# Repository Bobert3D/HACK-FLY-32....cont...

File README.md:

# HACK FLY 32 (3 inch fpv drone using esp32 s3)

A compact 3-inch 3D printed FPV drone designed for efficiency, stability, and extended flight time. This project features a custom-built flight controller, ExpressLRS (ELRS) communication, and GPS support, all running on Betaflight firmware.

**[Zine link](/docs/ZINE/HACK%20FLY%20ZINE.pdf)**

⚠️ Disclaimer
The use and operation of this drone may require licenses in certain countries. This project is experimental and provided without any guarantee of safety or reliability and it's under the [CERN Open Hardware Licence version 2-Strongly reciprocal ](/license), and the firmware ESP-FLY is under the MIT license.

USE AT YOUR OWN RISK.

# Specifications

Frame Size: 3-inch.

Motors: 1104 – 4300KV- (remix uses IFlight XING2 1404 4600KV!)

Propeller: Gemfan 3018 bi-blade(possible tri blade!).

Battery Support: 3S ONLY if running XING2 at 4600KV!! LiPo.

Suggested Batt: (900-1500)mah 3s lipo.

Flight Controller: Custom-designed FC. (Read more below!)

Firmware: Betaflight(not native running via ESP-FC)!

RC Protocol: ExpressLRS (ELRS)

Navigation: GPS supported.

GPS compatibility: Any 15*15mm gps (HGLRS M100 Mini suggested)

Use Case: Long-range FPV, but mostly FPV 4k cinematic action and camera.

# Why Hack Fly????

A custom hardware build including a PCB that gives you your own way to add spice to it!
Also compatible with BetaFlight (you can achieve very agile and stable flight characteristics). Supports all types of Radio RX protocols: PPM, SBUS, IBUS, and CRSF Receivers.
If you combine it with a high-performance 18650 Li-ion battery (like Molicel PB28A,Eve 30pl,Ampace jp30 or Sony vt6), you can get over 10 minutes of flight time!

Who doesn't want their drone to be repairable? The 3D-printed frame gives you that flexibility.
Break the frame in a crash? Just print another. Cost? Less than $1 even if you use PETG-CF.

# Documentation
In this repository, you can find 3D printable STL files, Garber and all the other
files to build your own flight controller and Drone frame. 
For flashing the latest Betaflight to the Flight controller visit rtlopez/esp-fc repo- 
**https://github.com/rtlopez/esp-fc**.

# Quick Start

## Requirements

## Hardware:

* Seeed Studio Xiao ESP32 S3(https://www.seeedstudio.com/XIAO-ESP32S3-p-5627.html)
* 1104 4300kv motor (or XIN 1404 4600KV, I used those!) x4 (https://shop.iflight.com/index.php?route=product/product&product_id=3382)
* 2-3S micro 8A ESC (or my custom PCB!) x4 (https://s.click.aliexpress.com/e/_c4ShBcjr)
> [!IMPORTANT]
> **If you also want build your own 4in1 esc**, Visit this repo- **https://github.com/minhazislamnafi/Nano-2-3s-AM32-ESC**.
* Gemfan 3018 bi-blade × 2 pair (https://s.click.aliexpress.com/e/_c34qvZlJ)
* Hglrc m100 mini GPS (https://s.click.aliexpress.com/e/_c4F9Fw8h)
* HGLRC Zeus Nano VTX 350mW (https://s.click.aliexpress.com/e/_c3wNfnSD)
* 2.54mm Round Hole Needle Female & Male Pin Header (https://s.click.aliexpress.com/e/_c327hfoV)
* For VRX buy any good 5.8ghz analog goggles (ranging from 70-300$) or Checkout Artlink digital system

**Components:**

* Mpu6050M QFN-24 (https://s.click.aliexpress.com/e/_c2JBpdQt)
* 0402 10uH inductor (https://s.click.aliexpress.com/e/_c3vbFmHj)
* Some 0603 size Resistors and capacitors [**Checkout Bill of material**](/Flight%20Controller/PCB/BOM_HACK_FLY_V1.2_2026-04-11.csv)
(https://a.aliexpress.com/_c3XHJm1T)
* 0805 size red & green led ×2
(https://s.click.aliexpress.com/e/_c3fRfz0V)

## For detailed parts list and prices follow [BOM](docs/Bill%20of%20material/BOM.md) ##

## PCB

Use JLCPCB if you're in ASIA or PCBWAY if you're in America. Also, find what manufacturer is better for you. 
If you just want to get Flight controller PCB then use this [**GERBER file**](/Flight%20Controller/PCB/Gerber_HACK_FLY_PCB_V1.2_2026-04-11.zip). Download it and place order.
Or if you just want to build your own PCB, then follow this [**Schematic**](/Flight%20Controller/PCB/Schematic_HACK_FLY_2026-04-11.svg).

## CAD Render

## Full Onshape CAD [link](https://cad.onshape.com/documents/91570ca427478f6ae70e01eb/w/492acaa76972d9ee5b32506f/e/992fe092f0691e5ff67f2b14?renderMode=0&uiState=69eeb3fd4989f512fbb6f874)/[Full assembly](https://cad.onshape.com/documents/91570ca427478f6ae70e01eb/w/492acaa76972d9ee5b32506f/e/0d19368f0521a092eb10a81c?renderMode=0&uiState=69feb6588dc385fd419da8b7)

To print all the parts for the HACK FLY frame, please **USE**

**PETG or ABS** - [Top plate](/Drone%20Frame/Top%20Plate/Top%20plate.stl), [Bottom plate](/Drone%20Frame/Bottom%20plate).(**better to use PETG-CF**)

**TPU** - [Camera mount](/Drone%20Frame/Camera%20Mount/Camera%20mount%20right.stl), [GPS mount](/Drone%20Frame/GPS%20mount/GPS%20mount.stl), [VTXantena mount](/Drone%20Frame/Vtx%20antena%20mount/Antenna%20mount.stl).

## IRL

## Wiring Diagram ##

## AFTER EVERYTHING IS DONE SOURCING, FOLLOW THESE STEPS ##

**1. Spend some money $$ to buy the parts mentioned in [BOM](docs/Bill%20of%20material/BOM.md).**

**2. Order the Flight controller PCB using this [GERBER file](/Flight%20Controller/PCB/Gerber_HACK_FLY_PCB_V1.2_2026-04-11.zip).**

**3. Solder the SMD components of the PCB by hand ;) Or just order the PCBs with SMT services.**

**4. Using the wiring diagram, solder the ESCs and battery connector to the PCB.**

**5. crucial step: assemble everything. ( I will add every assembly step, once I have built IRL:)**

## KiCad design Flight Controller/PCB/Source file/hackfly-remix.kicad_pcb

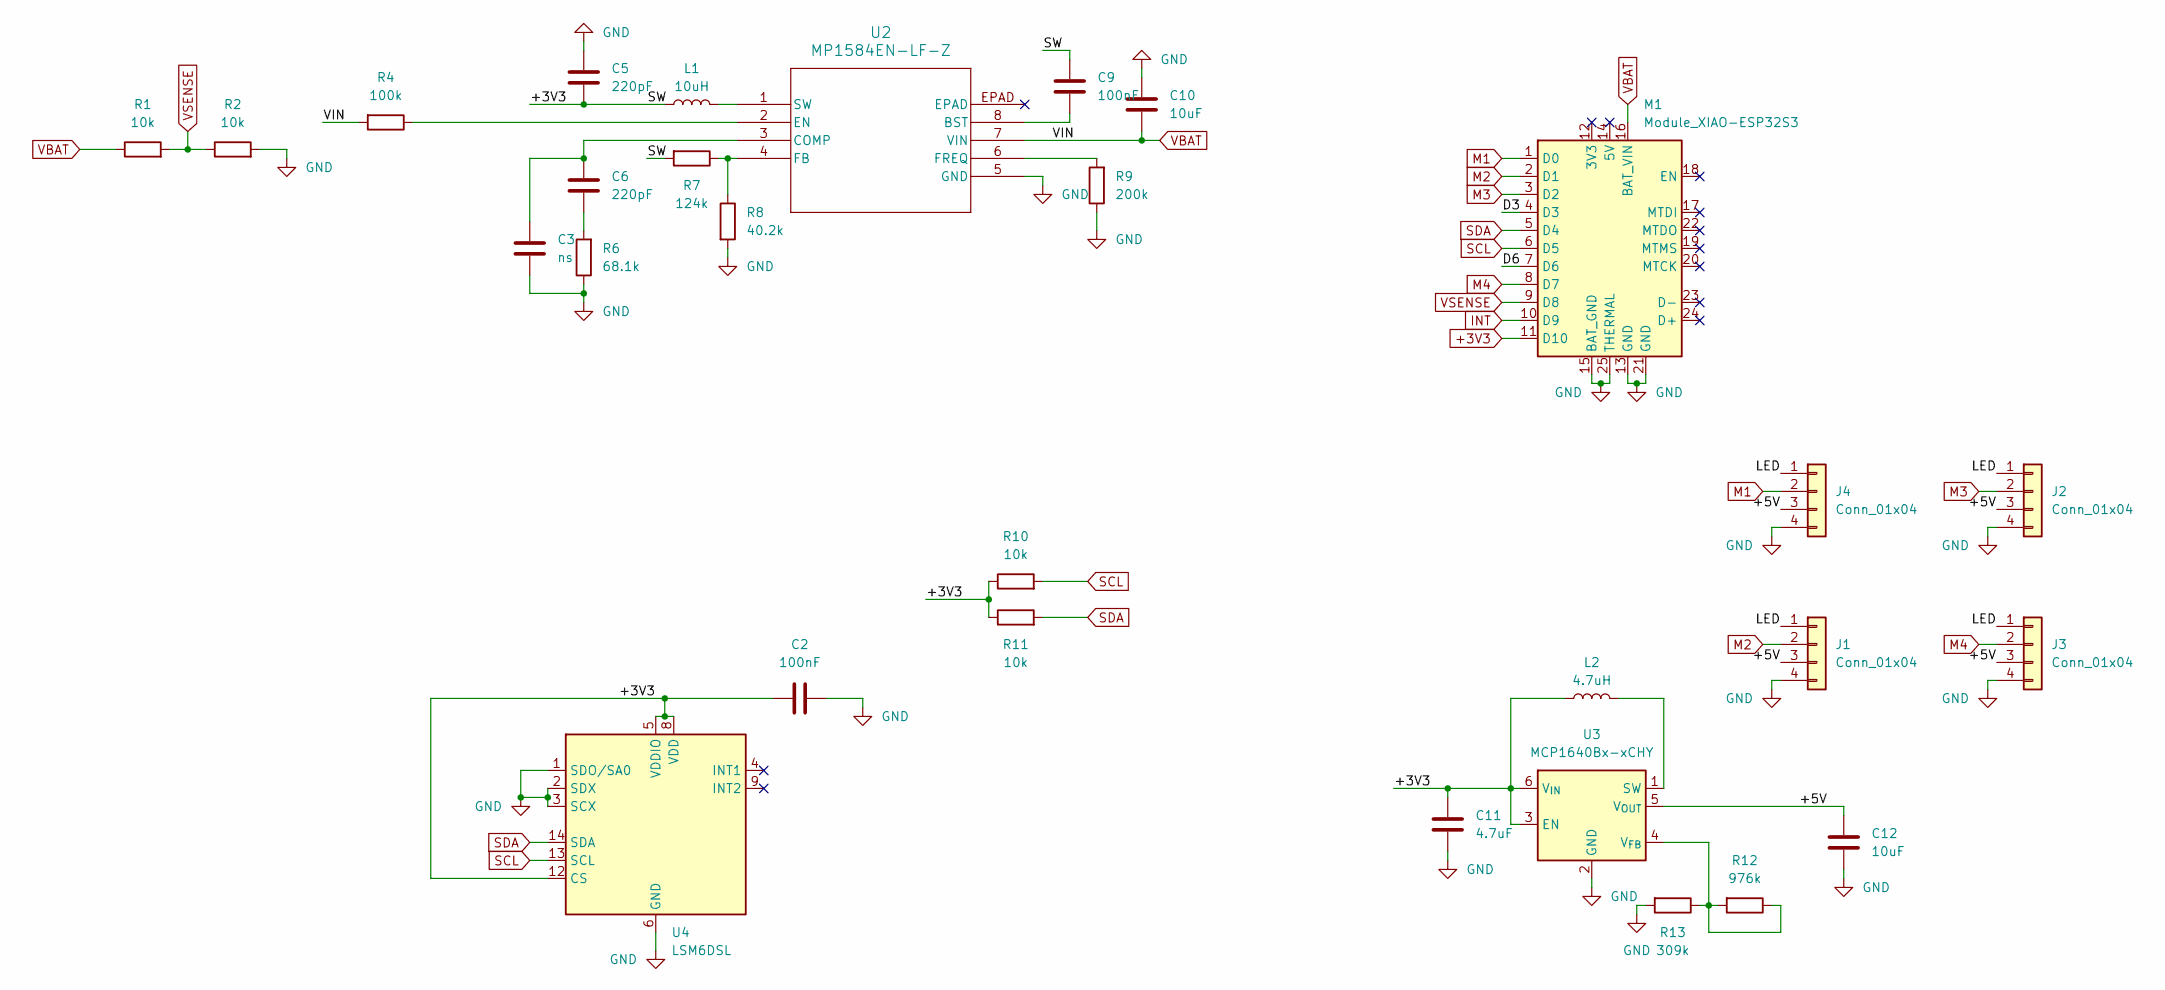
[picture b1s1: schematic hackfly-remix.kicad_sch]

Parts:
C2, C9: 100nF; C_0805_2012Metric
C3: ns; C_0805_2012Metric
C5, C6: 220pF; C_0805_2012Metric
C10, C12: 10uF; C_0805_2012Metric
C11: 4.7uF; C_0805_2012Metric
J1, J2, J3, J4: Conn_01x04; PinHeader_1x04_P1.27mm_Vertical
L1: 10uH; L_1206_3216Metric
L2: 4.7uH; L_1206_3216Metric
M1: Module_XIAO-ESP32S3; SeeedStudio_XIAO_ESP32S3
R1, R2, R10, R11: 10k; R_0805_2012Metric
R4: 100k; R_0805_2012Metric
R6: 68.1k; R_0805_2012Metric
R7: 124k; R_0805_2012Metric
R8: 40.2k; R_0805_2012Metric
R9: 200k; R_0805_2012Metric
R12: 976k; R_0805_2012Metric
R13: 309k; R_0805_2012Metric
U2: MP1584EN-LF-Z; SOIC8E_MPS
U3: MCP1640Bx-xCHY; SOT-23-6
U4: LSM6DSL; LGA-14_3x2.5mm_P0.5mm_LayoutBorder3x4y

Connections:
+3V3: C2.1, C5.1, C9.2, C11.2, L1.1, L2.1, M1.11 (D10), R7.2, R10.1, R11.1, U3.3 (EN), U3.6 (V_{IN}), U4.5 (VDDIO), U4.8 (VDD), U4.12 (CS)
/+5V: C12.2, J1.3, J2.3, J3.3, J4.3, U3.5 (V_{OUT})
/D3: M1.4 (D3)
/D6: M1.7 (D6)
/LED: J1.1, J2.1, J3.1, J4.1
GND: C2.2, C3.1, C5.2, C10.2, C11.1, C12.1, J1.4, J2.4, J3.4, J4.4, M1.13 (GND), M1.15 (BAT_GND), M1.21 (GND), M1.25 (THERMAL), R2.2, R6.1, R8.2, R9.1, R13.2, U2.5 (GND), U3.2 (GND), U4.1 (SDO/SA0), U4.2 (SDX), U4.3 (SCX), U4.6 (GND), U4.7 (GND)
INT: M1.10 (D9)
M1: J4.2, M1.1 (D0)
M2: J1.2, M1.2 (D1)
M3: J2.2, M1.3 (D2)
M4: J3.2, M1.8 (D7)
unnamed: C6.1, R6.2
unnamed: C9.1, U2.8 (BST)
unnamed: C3.2, C6.2, U2.3 (COMP)
unnamed: R4.1, U2.2 (EN)
unnamed: R7.1, R8.1, U2.4 (FB)
unnamed: R9.2, U2.6 (FREQ)
unnamed: L1.2, U2.1 (SW)
unnamed: L2.2, U3.1 (SW)
unnamed: R12.1, R12.2, R13.1, U3.4 (V_{FB})
SCL: M1.6 (D5), R10.2, U4.13 (SCL)
SDA: M1.5 (D4), R11.2, U4.14 (SDA)
VBAT: C10.1, M1.16 (BAT_VIN), R1.1, R4.2, U2.7 (VIN)
VSENSE: M1.9 (D8), R1.2, R2.1

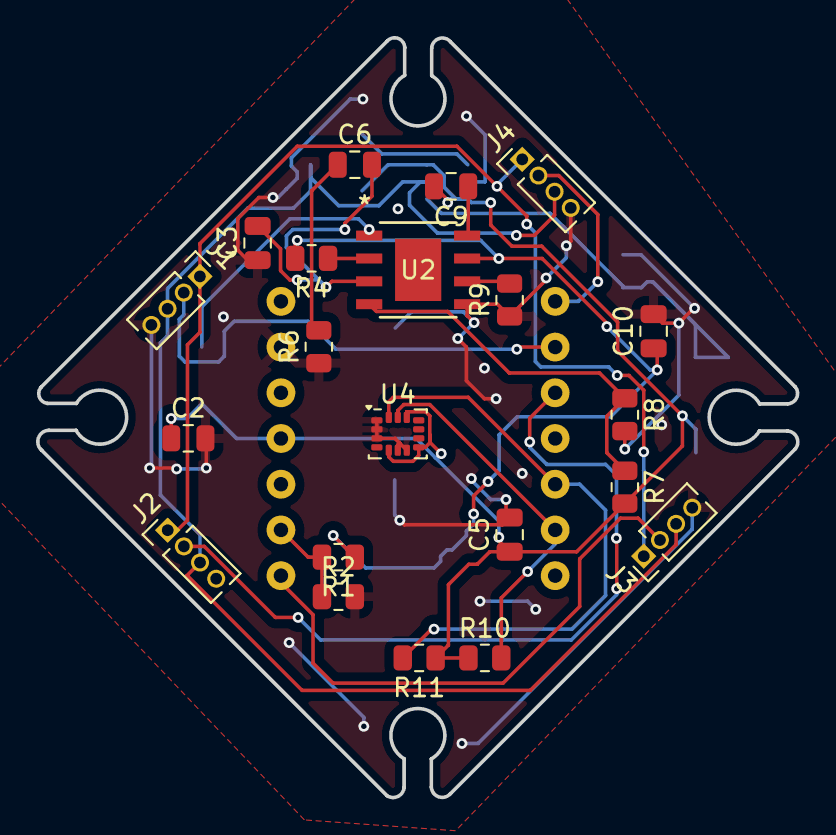
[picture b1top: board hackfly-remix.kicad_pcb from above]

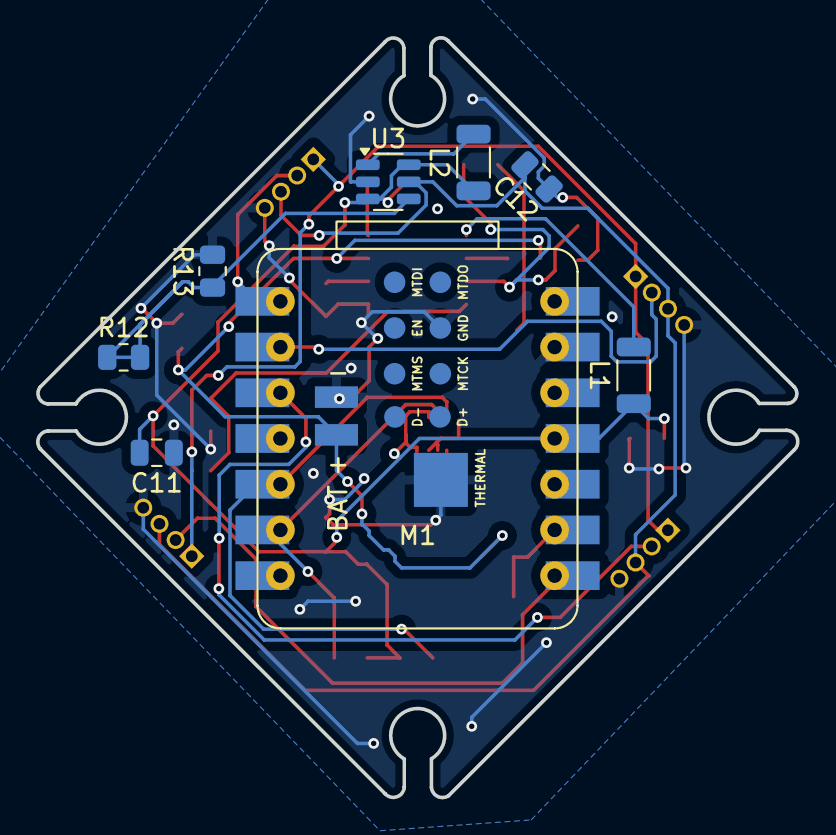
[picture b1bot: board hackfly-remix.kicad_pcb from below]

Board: 2 copper layers, 42.2 x 42.2 mm, 29 parts (8 on the bottom side), 21 nets.

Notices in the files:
README.md:
License: OHL v2
